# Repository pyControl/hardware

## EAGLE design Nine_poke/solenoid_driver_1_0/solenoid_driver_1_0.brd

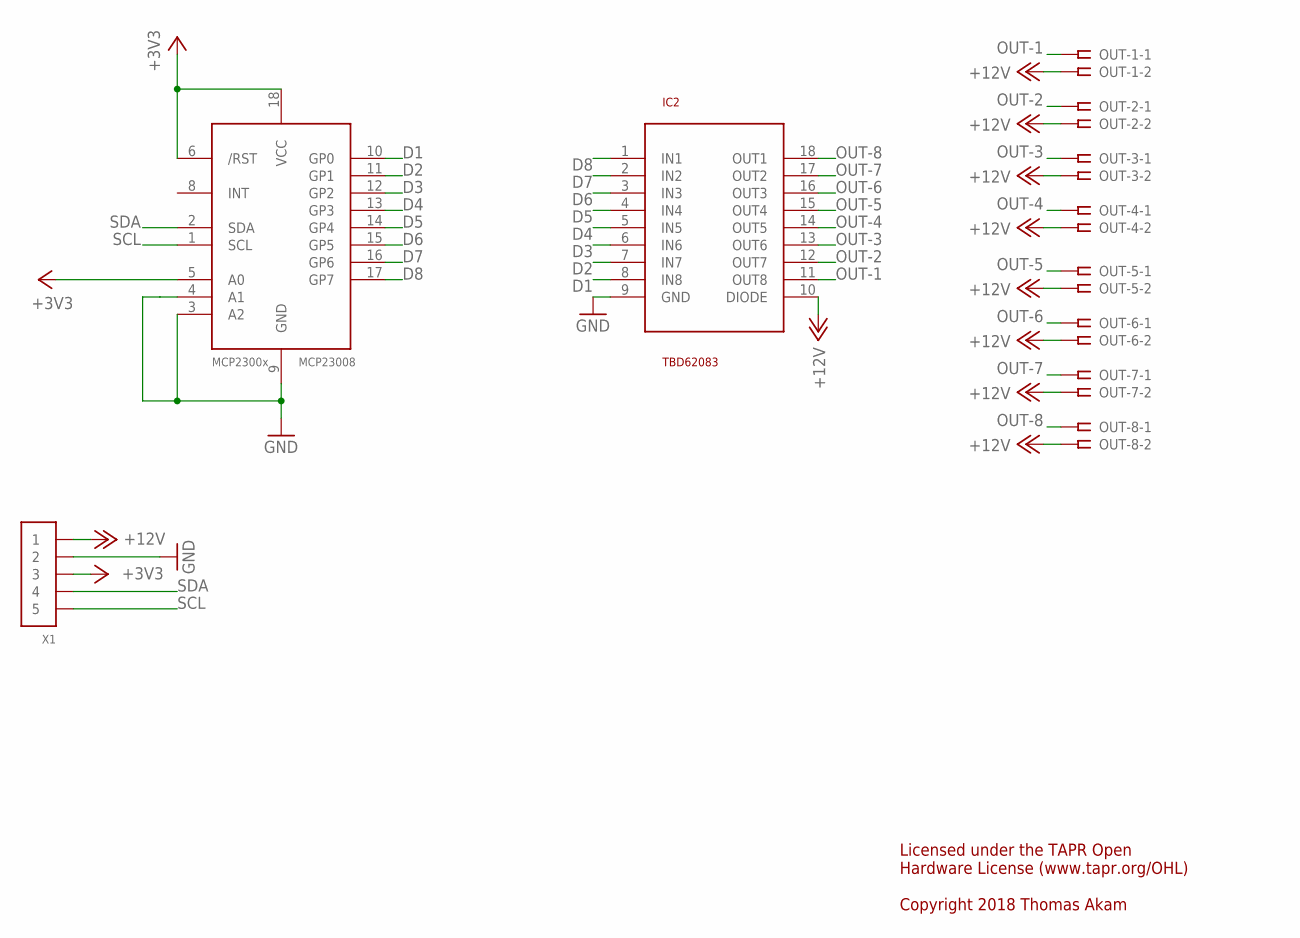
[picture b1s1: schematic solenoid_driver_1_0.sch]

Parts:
IC2: TBD62083; SO18L
MCP23008: MCP2300X/SO; SO18W
OUT-1, OUT-2, OUT-3, OUT-4, OUT-5, OUT-6, OUT-7, OUT-8: SSW-102-02-S-S-RA
X1: CONN_5-1-53261; PB-53261-05

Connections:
+3V3: MCP23008.5 (A0), MCP23008.6 (/RST), MCP23008.18 (VCC), X1.3
+12V: IC2.10 (DIODE), OUT-1.2, OUT-2.2, OUT-3.2, OUT-4.2, OUT-5.2, OUT-6.2, OUT-7.2, OUT-8.2, X1.1
D1: IC2.8 (IN8), MCP23008.10 (GP0)
D2: IC2.7 (IN7), MCP23008.11 (GP1)
D3: IC2.6 (IN6), MCP23008.12 (GP2)
D4: IC2.5 (IN5), MCP23008.13 (GP3)
D5: IC2.4 (IN4), MCP23008.14 (GP4)
D6: IC2.3 (IN3), MCP23008.15 (GP5)
D7: IC2.2 (IN2), MCP23008.16 (GP6)
D8: IC2.1 (IN1), MCP23008.17 (GP7)
GND: IC2.9 (GND), MCP23008.3 (A2), MCP23008.4 (A1), MCP23008.9 (GND), X1.2
OUT-1: IC2.11 (OUT8), OUT-1.1
OUT-2: IC2.12 (OUT7), OUT-2.1
OUT-3: IC2.13 (OUT6), OUT-3.1
OUT-4: IC2.14 (OUT5), OUT-4.1
OUT-5: IC2.15 (OUT4), OUT-5.1
OUT-6: IC2.16 (OUT3), OUT-6.1
OUT-7: IC2.17 (OUT2), OUT-7.1
OUT-8: IC2.18 (OUT1), OUT-8.1
SCL: MCP23008.1 (SCL), X1.5
SDA: MCP23008.2 (SDA), X1.4

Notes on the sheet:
Licensed under the TAPR Open Hardware License (www.tapr.org/OHL) Copyright 2018 Thomas Akam

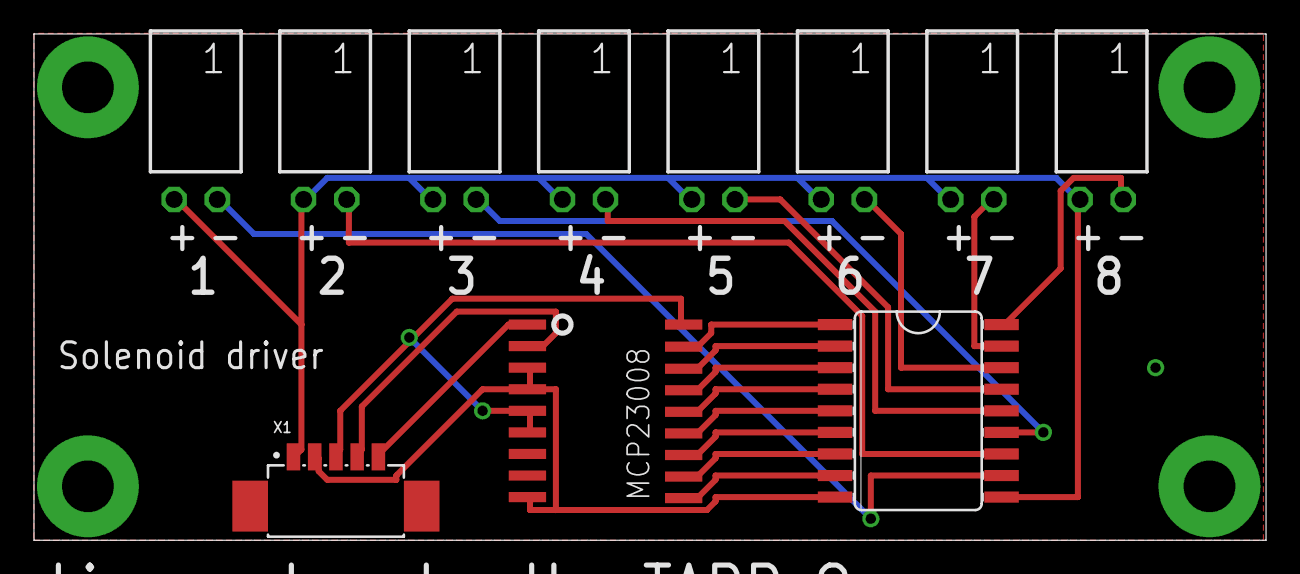
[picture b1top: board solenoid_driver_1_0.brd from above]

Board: 2 copper layers, 72.5 x 29.8 mm, 11 parts (0 on the bottom side), 21 nets.

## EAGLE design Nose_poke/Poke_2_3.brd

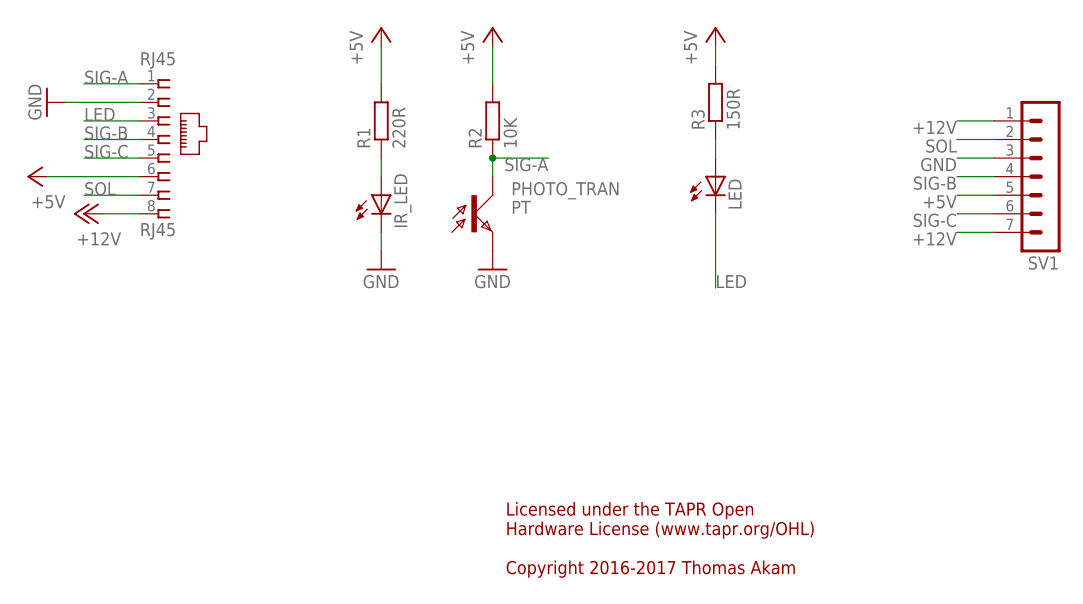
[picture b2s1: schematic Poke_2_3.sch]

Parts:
IR_LED: LEDIRL80A; IRL80A
LED: LEDSML0805; SML0805
PHOTO_TRAN: PT; LPT80A
R1: 220R; R0805
R2: 10K; M0805
R3: 150R; M0805
RJ45: RJ45; RJ45-NO-SHIELD-VERTICAL
SV1: MA07-1

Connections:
+5V: R1.2, R2.2, R3.2, RJ45.6, SV1.5
+12V: RJ45.8, SV1.1, SV1.7
GND: IR_LED.K (C), PHOTO_TRAN.E, RJ45.2, SV1.3
LED: LED.C, RJ45.3
unnamed: IR_LED.A, R1.1
unnamed: LED.A, R3.1
SIG-A: PHOTO_TRAN.C, R2.1, RJ45.1
SIG-B: RJ45.4, SV1.4
SIG-C: RJ45.5, SV1.6
SOL: RJ45.7, SV1.2

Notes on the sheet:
Licensed under the TAPR Open Hardware License (www.tapr.org/OHL) Copyright 2016-2017 Thomas Akam

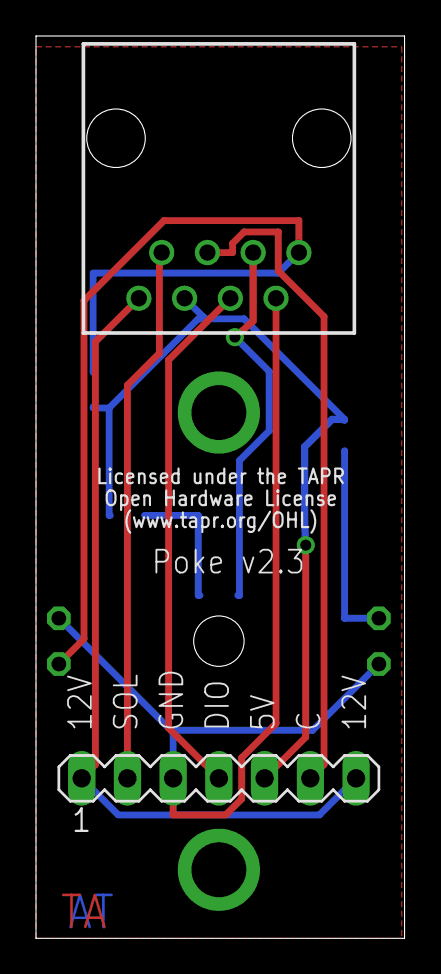
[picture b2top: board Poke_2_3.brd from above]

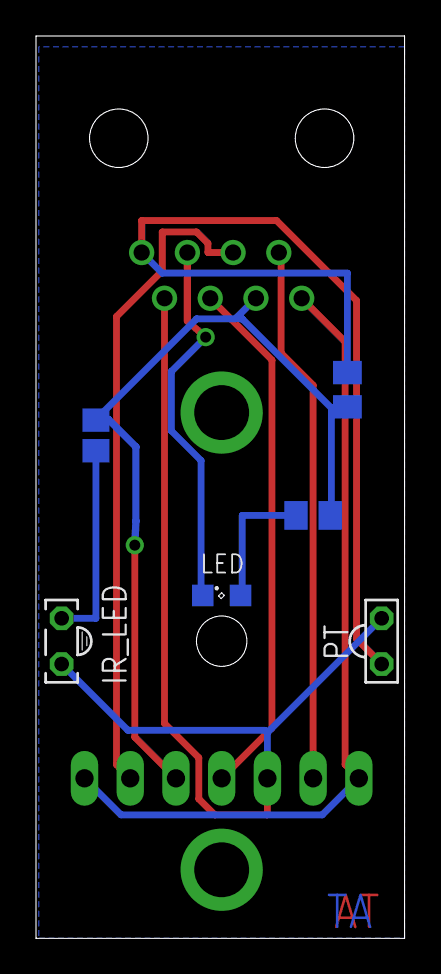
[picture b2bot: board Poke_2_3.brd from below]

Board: 2 copper layers, 20.5 x 50.1 mm, 8 parts (6 on the bottom side), 10 nets.

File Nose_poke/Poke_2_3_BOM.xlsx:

Electronic components
Part | Value | Device | Package | Description | MF | MPN | OC_FARNELL
IR_LED |  | - | - | IR LED side | Sharp | GL480E00000F | 9707794
PHOTO_TRAN |  | - | - | PHOTO TRANSISTOR | OSRAM | SFH3100F-1-Z | 1226443
LED |  | - | 0805 | LED white 0805 | MULTICOMP | OVS-0801 | 1716764
R1 | 220R | - | 0805 | RESISTOR 0805 | MULTICOMP | MC01W08051220R | 9332804
R2 | 10K | - | 0805 | RESISTOR 0805 | MULTICOMP | MC01W0805510K | 9333720
R3 | 150R | - | 0805 | RESISTOR 0805 | MULTICOMP | MC01W08051150R | 9332596
SV1 |  | - | - | Receptacle | AMPHENOL FCI | 76341-307LF | 1098037
RJ45 |  | RJ45VERTICAL | RJ45VERTICAL | RJ45VERTICAL | TE CONNECTIVITY | 5556416-1 | 1773034
Mechanical components
Laser cut plasctic parts as detailed in plastic_parts.pdf
Bolt m3 20mm |  |  |  |  |  |  | 1419947
Bolt m3 20mm |  |  |  |  |  |  | 1419947
Nut m3 |  |  |  |  |  |  | 1420788
Nut m3 |  |  |  |  |  |  | 1420788
Spacer m3, 3mm |  |  |  |  |  |  | 359154
Spacer m3, 3mm |  |  |  |  |  |  | 359154
Licensed under the TAPR Open Hardware License (www.tapr.org/OHL)
Copyright 2016-2017 Thomas Akam

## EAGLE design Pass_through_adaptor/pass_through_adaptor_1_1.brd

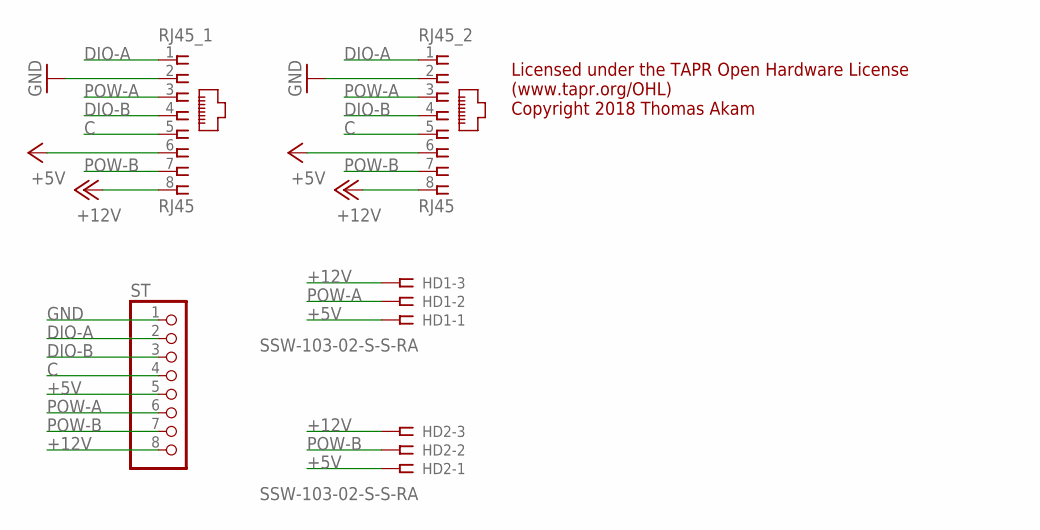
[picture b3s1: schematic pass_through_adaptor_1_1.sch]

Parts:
HD1, HD2: SSW-103-02-S-S-RA
RJ45_1, RJ45_2: RJ45; RJ45-NO-SHIELD-VERTICAL
ST: PINHD-1X8; 1X08

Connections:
+5V: HD1.1, HD2.1, RJ45_1.6, RJ45_2.6, ST.5
+12V: HD1.3, HD2.3, RJ45_1.8, RJ45_2.8, ST.8
C: RJ45_1.5, RJ45_2.5, ST.4
DIO-A: RJ45_1.1, RJ45_2.1, ST.2
DIO-B: RJ45_1.4, RJ45_2.4, ST.3
GND: RJ45_1.2, RJ45_2.2, ST.1
POW-A: HD1.2, RJ45_1.3, RJ45_2.3, ST.6
POW-B: HD2.2, RJ45_1.7, RJ45_2.7, ST.7

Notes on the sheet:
Licensed under the TAPR Open Hardware License (www.tapr.org/OHL) Copyright 2018 Thomas Akam

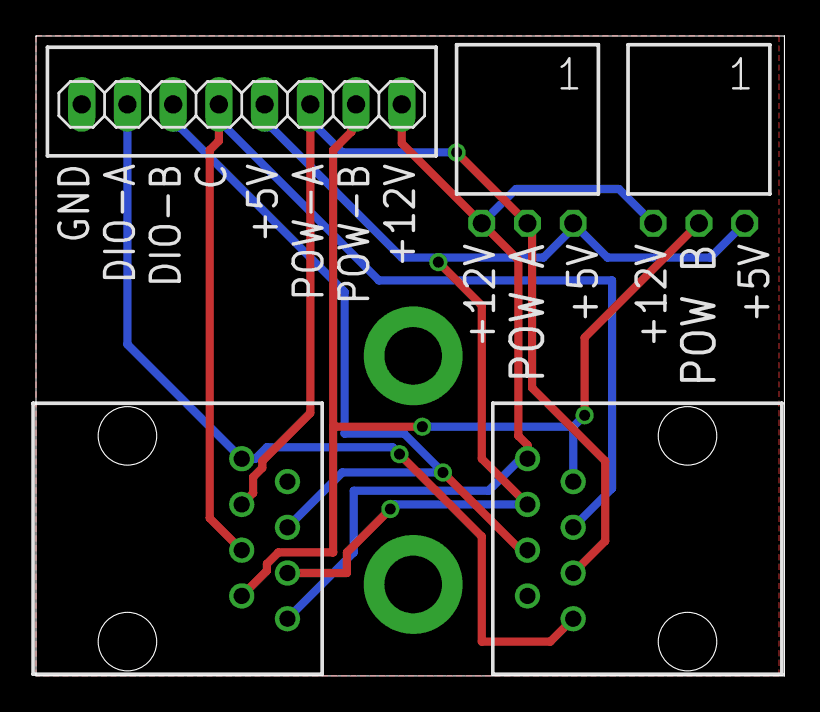
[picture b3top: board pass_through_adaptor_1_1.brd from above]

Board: 2 copper layers, 41.6 x 35.5 mm, 5 parts (0 on the bottom side), 8 nets.

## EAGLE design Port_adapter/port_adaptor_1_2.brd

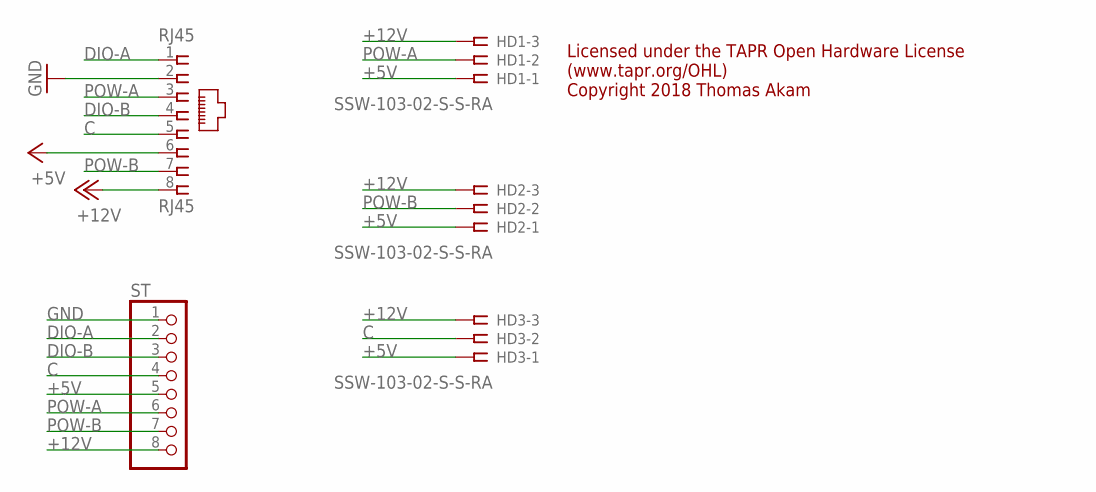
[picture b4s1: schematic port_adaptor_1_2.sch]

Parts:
HD1, HD2, HD3: SSW-103-02-S-S-RA
RJ45: RJ45; RJ45-NO-SHIELD-VERTICAL
ST: PINHD-1X8; 1X08

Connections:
+5V: HD1.1, HD2.1, HD3.1, RJ45.6, ST.5
+12V: HD1.3, HD2.3, HD3.3, RJ45.8, ST.8
C: HD3.2, RJ45.5, ST.4
DIO-A: RJ45.1, ST.2
DIO-B: RJ45.4, ST.3
GND: RJ45.2, ST.1
POW-A: HD1.2, RJ45.3, ST.6
POW-B: HD2.2, RJ45.7, ST.7

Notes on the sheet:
Licensed under the TAPR Open Hardware License (www.tapr.org/OHL) Copyright 2018 Thomas Akam

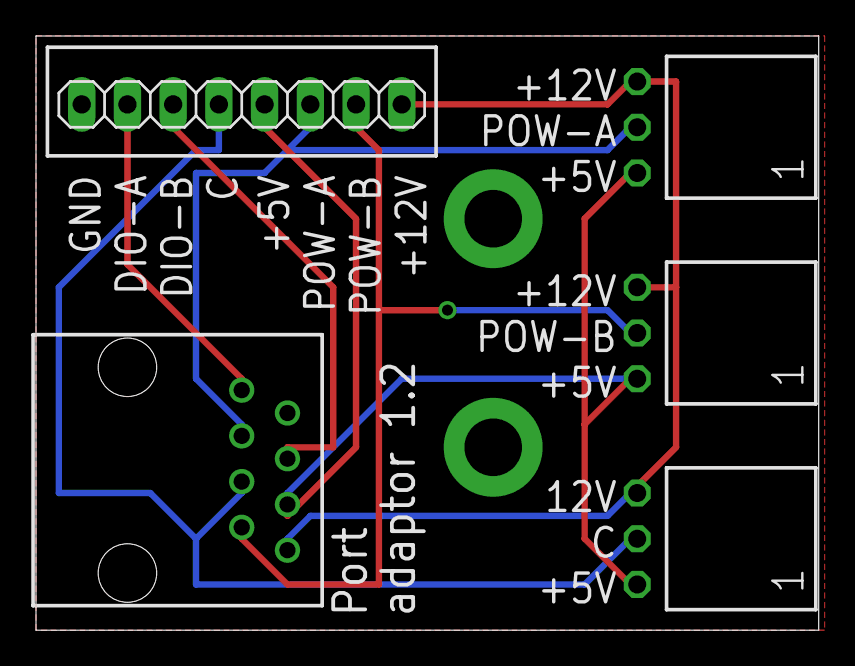
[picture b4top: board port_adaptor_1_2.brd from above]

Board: 2 copper layers, 43.5 x 33.0 mm, 5 parts (0 on the bottom side), 8 nets.

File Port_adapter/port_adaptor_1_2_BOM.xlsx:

Part | Value | Device | Package | Description | MF | MPN | OC_FARNELL
HD1 | - | - | - | 3 way female header RA | SAMTEC | SSW-103-02-T-S-RA | 1803357
HD2 | - | - | - | 3 way female header RA | SAMTEC | SSW-103-02-T-S-RA | 1803357
HD3 | - | - | - | 3 way female header RA | SAMTEC | SSW-103-02-T-S-RA | 1803357
RJ45 | - | - | - | RJ45Horisontal | TE CONNECTIVITY | 215877-1 | 3363144
ST | - | - | - | Screw terminal | PHOENIX CONTACT | 1725711 | 3041438
Licensed under the TAPR Open Hardware License
(www.tapr.org/OHL)
Copyright 2018 Thomas Akam

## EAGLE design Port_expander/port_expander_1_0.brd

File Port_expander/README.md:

# Port Expander

The port expander board uses i2c serial to parallel IO expander ICs to run 8 behaviour ports from a single behaviour port on the breakout board.  

[Documentation](https://pycontrol.readthedocs.io/en/latest/user-guide/hardware/#port-expander)

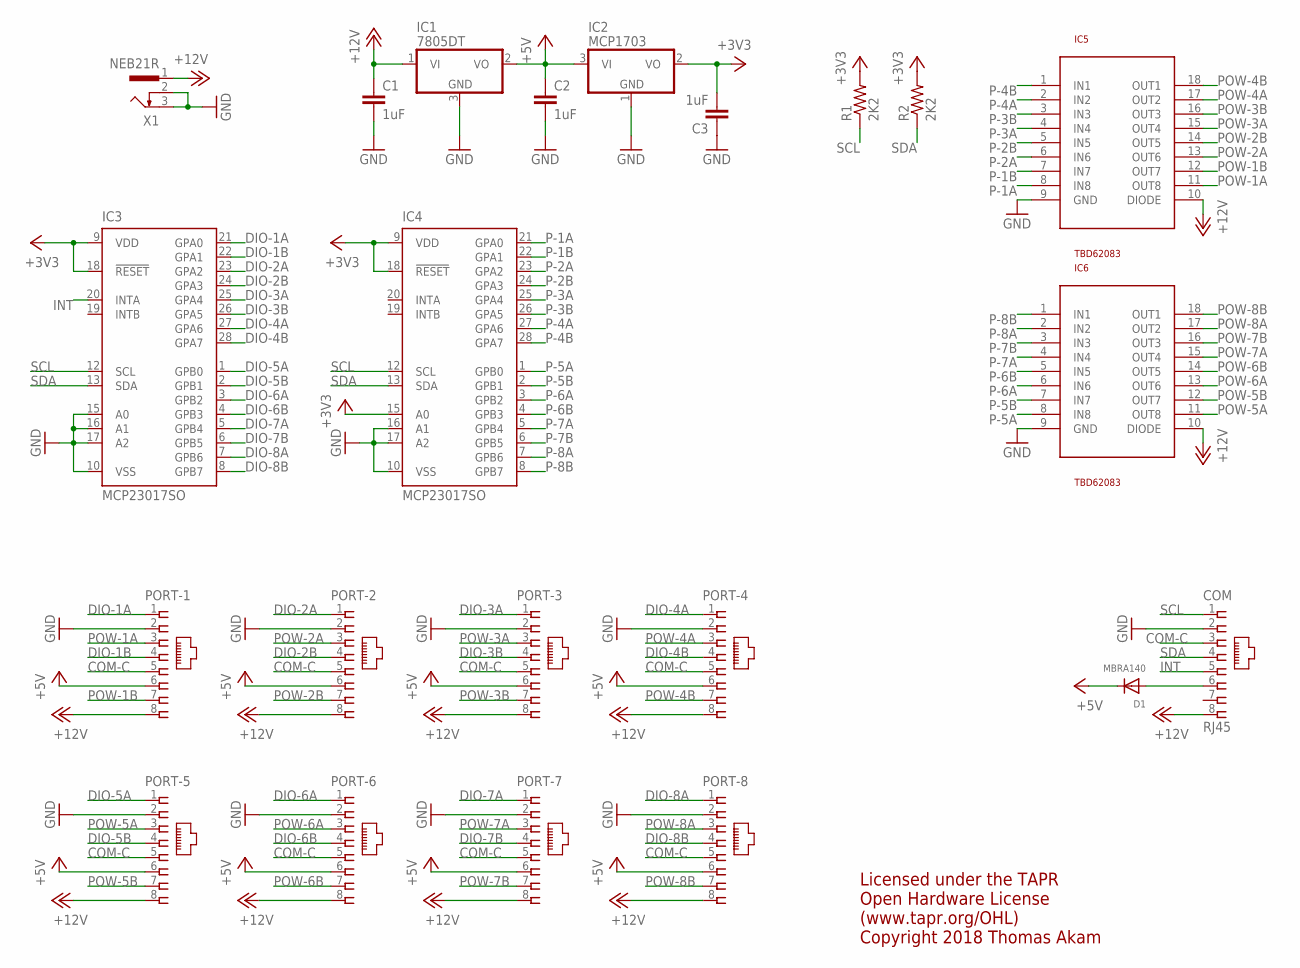
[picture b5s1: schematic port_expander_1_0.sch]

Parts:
C1, C2, C3: 1uF; C0805
COM: RJ45; RJ45-NO-SHIELD-VERTICAL
D1: MBRA140; SOD-123
IC1: 7805DT; TO252
IC2: MCP1703; SOT23
IC3, IC4: MCP23017SO; SO28W
IC5, IC6: TBD62083; SO18L
PORT-1, PORT-2, PORT-3, PORT-4, PORT-5, PORT-6, PORT-7, PORT-8: RJ45VERTICAL; RJ45-NO-SHIELD-VERTICAL
R1, R2: 2K2; 0805
X1: NEB21R

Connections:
+3V3: C3.2, IC2.2 (VO), IC3.9 (VDD), IC3.18 (!RESET), IC4.9 (VDD), IC4.15 (A0), IC4.18 (!RESET), R1.2, R2.2
+5V: C2.1, D1.C, IC1.2 (VO), IC2.3 (VI), PORT-1.6, PORT-2.6, PORT-3.6, PORT-4.6, PORT-5.6, PORT-6.6, PORT-7.6, PORT-8.6
+12V: C1.1, COM.8, IC1.1 (VI), IC5.10 (DIODE), IC6.10 (DIODE), PORT-1.8, PORT-2.8, PORT-3.8, PORT-4.8, PORT-5.8, PORT-6.8, PORT-7.8, PORT-8.8, X1.1
COM-C: COM.3, PORT-1.5, PORT-2.5, PORT-3.5, PORT-4.5, PORT-5.5, PORT-6.5, PORT-7.5, PORT-8.5
DIO-1A: IC3.21 (GPA0), PORT-1.1
DIO-1B: IC3.22 (GPA1), PORT-1.4
DIO-2A: IC3.23 (GPA2), PORT-2.1
DIO-2B: IC3.24 (GPA3), PORT-2.4
DIO-3A: IC3.25 (GPA4), PORT-3.1
DIO-3B: IC3.26 (GPA5), PORT-3.4
DIO-4A: IC3.27 (GPA6), PORT-4.1
DIO-4B: IC3.28 (GPA7), PORT-4.4
DIO-5A: IC3.1 (GPB0), PORT-5.1
DIO-5B: IC3.2 (GPB1), PORT-5.4
DIO-6A: IC3.3 (GPB2), PORT-6.1
DIO-6B: IC3.4 (GPB3), PORT-6.4
DIO-7A: IC3.5 (GPB4), PORT-7.1
DIO-7B: IC3.6 (GPB5), PORT-7.4
DIO-8A: IC3.7 (GPB6), PORT-8.1
DIO-8B: IC3.8 (GPB7), PORT-8.4
GND: C1.2, C2.2, C3.1, COM.2, IC1.3 (GND), IC2.1 (GND), IC3.10 (VSS), IC3.15 (A0), IC3.16 (A1), IC3.17 (A2), IC4.10 (VSS), IC4.16 (A1), IC4.17 (A2), IC5.9 (GND), IC6.9 (GND), PORT-1.2, PORT-2.2, PORT-3.2, PORT-4.2, PORT-5.2, PORT-6.2, PORT-7.2, PORT-8.2, X1.2, X1.3
INT: COM.5, IC3.20 (INTA)
unnamed: COM.6, D1.A
P-1A: IC4.21 (GPA0), IC5.8 (IN8)
P-1B: IC4.22 (GPA1), IC5.7 (IN7)
P-2A: IC4.23 (GPA2), IC5.6 (IN6)
P-2B: IC4.24 (GPA3), IC5.5 (IN5)
P-3A: IC4.25 (GPA4), IC5.4 (IN4)
P-3B: IC4.26 (GPA5), IC5.3 (IN3)
P-4A: IC4.27 (GPA6), IC5.2 (IN2)
P-4B: IC4.28 (GPA7), IC5.1 (IN1)
P-5A: IC4.1 (GPB0), IC6.8 (IN8)
P-5B: IC4.2 (GPB1), IC6.7 (IN7)
P-6A: IC4.3 (GPB2), IC6.6 (IN6)
P-6B: IC4.4 (GPB3), IC6.5 (IN5)
P-7A: IC4.5 (GPB4), IC6.4 (IN4)
P-7B: IC4.6 (GPB5), IC6.3 (IN3)
P-8A: IC4.7 (GPB6), IC6.2 (IN2)
P-8B: IC4.8 (GPB7), IC6.1 (IN1)
POW-1A: IC5.11 (OUT8), PORT-1.3
POW-1B: IC5.12 (OUT7), PORT-1.7
POW-2A: IC5.13 (OUT6), PORT-2.3
POW-2B: IC5.14 (OUT5), PORT-2.7
POW-3A: IC5.15 (OUT4), PORT-3.3
POW-3B: IC5.16 (OUT3), PORT-3.7
POW-4A: IC5.17 (OUT2), PORT-4.3
POW-4B: IC5.18 (OUT1), PORT-4.7
POW-5A: IC6.11 (OUT8), PORT-5.3
POW-5B: IC6.12 (OUT7), PORT-5.7
POW-6A: IC6.13 (OUT6), PORT-6.3
POW-6B: IC6.14 (OUT5), PORT-6.7
POW-7A: IC6.15 (OUT4), PORT-7.3
POW-7B: IC6.16 (OUT3), PORT-7.7
POW-8A: IC6.17 (OUT2), PORT-8.3
POW-8B: IC6.18 (OUT1), PORT-8.7
SCL: COM.1, IC3.12 (SCL), IC4.12 (SCL), R1.1
SDA: COM.4, IC3.13 (SDA), IC4.13 (SDA), R2.1

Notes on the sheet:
Licensed under the TAPR Open Hardware License (www.tapr.org/OHL) Copyright 2018 Thomas Akam

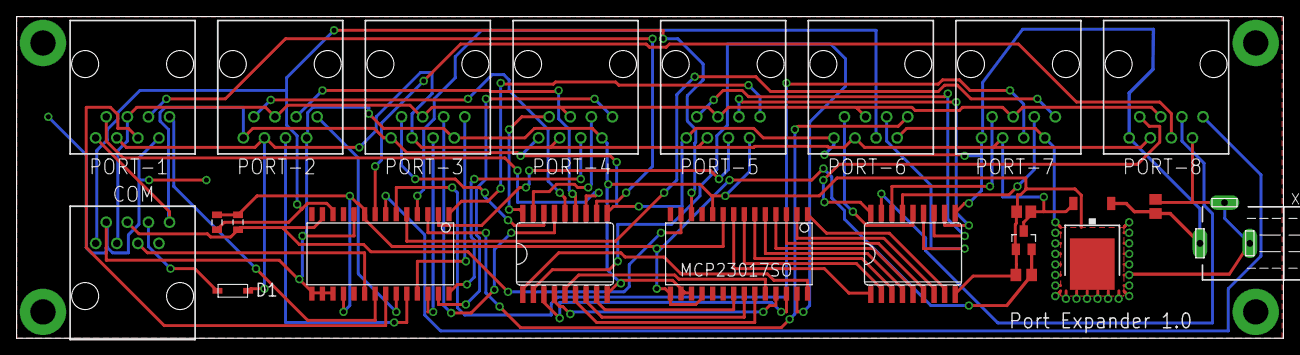
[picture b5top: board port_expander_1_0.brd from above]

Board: 2 copper layers, 152.6 x 38.7 mm, 22 parts (0 on the bottom side), 57 nets.

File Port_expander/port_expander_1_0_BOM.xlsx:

Part | Value | Device | Package | Description | MF | MPN | OC_FARNELL
R1 | 2K2 | - | 0805 | Resistor 0805 | Multicomp | MCWR08X2201FTL | 2447623
R2 | 2K2 | - | 0805 | Resistor 0805 | Multicomp | MCWR08X2201FTL | 2447623
C1 | 1uF | - | 0805 | capacitor 0805 | Multicomp | MC0805B105K250CT | 2320827
C2 | 1uF | - | 0805 | capacitor 0805 | Multicomp | MC0805B105K250CT | 2320827
C3 | 1uF | - | 0805 | capacitor 0805 | Multicomp | MC0805B105K250CT | 2320827
D1 | - | - | SOD-123FL | DIODE | ON SEMICONDUCTOR | MBR120VLSFT3G | 2533227
IC1 | - | 7805 | TO-252-3 | VOLTAGE REGULATOR | ON SEMICONDUCTOR | MC7805BDTRKG | 1652297
IC2 | - | MCP1703T | SOT-23 | Voltage regulator 3v3 | MICROCHIP | MCP1703T-3302E/CB | 1439518
IC3 | - | MCP23017 | SO28 | i2c port expander | MICROCHIP | MCP23017-E/SO | 1332087
IC4 | - | MCP23017 | SO28 | i2c port expander | MICROCHIP | MCP23017-E/SO | 1332087
IC5 |  | TBD62083 | SO18 | Low side driver | Toshiba | TBD62083AFG | -
IC6 |  | TBD62083 | SO18 | Low side driver | Toshiba | TBD62083AFG | -
PORT1 |  | - | - | RJ45Horisontal | TE CONNECTIVITY | 215877-1 | 3363144
PORT2 |  | - | - | RJ45Horisontal | TE CONNECTIVITY | 215877-1 | 3363144
PORT3 |  | - | - | RJ45Horisontal | TE CONNECTIVITY | 215877-1 | 3363144
PORT4 |  | - | - | RJ45Horisontal | TE CONNECTIVITY | 215877-1 | 3363144
PORT5 |  | - | - | RJ45Horisontal | TE CONNECTIVITY | 215877-1 | 3363144
PORT6 |  | - | - | RJ45Horisontal | TE CONNECTIVITY | 215877-1 | 3363144
PORT7 |  | - | - | RJ45Horisontal | TE CONNECTIVITY | 215877-1 | 3363144
PORT8 |  | - | - | RJ45Horisontal | TE CONNECTIVITY | 215877-1 | 3363144
COM |  | - | - | RJ45Horisontal | TE CONNECTIVITY | 215877-1 | 3363144
POW_CON |  | NEB21R | NEB21R | 2.1mm socket | Lumberg | NEB 21 R | 1217037
Licensed under the TAPR Open Hardware License (www.tapr.org/OHL)
Copyright 2018 Thomas Akam

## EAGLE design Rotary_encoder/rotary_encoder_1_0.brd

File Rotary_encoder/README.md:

# Rotary encoder

Board for connecting an Avago HEDM or HEDS series rotary encoder to a pyControl behaviour port.

[Documentation](https://pycontrol.readthedocs.io/en/latest/user-guide/hardware/#rotary-encoder)

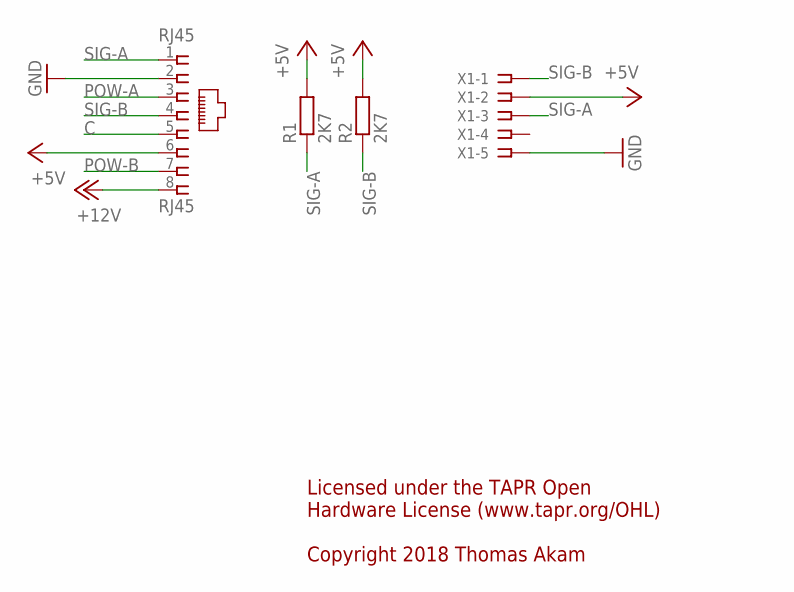
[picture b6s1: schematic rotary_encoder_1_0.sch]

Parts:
R1, R2: 2K7; M0805
RJ45: RJ45; RJ45-NO-SHIELD-VERTICAL
X1: SSW-105-02-S-S-RA

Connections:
+5V: R1.2, R2.2, RJ45.6, X1.2
+12V: RJ45.8
C: RJ45.5
GND: RJ45.2, X1.5
POW-A: RJ45.3
POW-B: RJ45.7
SIG-A: R1.1, RJ45.1, X1.3
SIG-B: R2.1, RJ45.4, X1.1

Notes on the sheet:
Licensed under the TAPR Open Hardware License (www.tapr.org/OHL) Copyright 2018 Thomas Akam

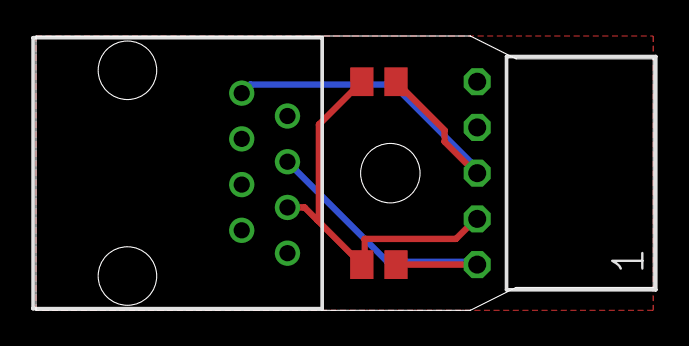
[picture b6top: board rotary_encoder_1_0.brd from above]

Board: 2 copper layers, 34.3 x 15.2 mm, 4 parts (0 on the bottom side), 4 nets.

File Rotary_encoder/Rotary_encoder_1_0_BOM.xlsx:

Part | Value | Device | Package | Description | MF | MPN | OC_FARNELL
X1 | - | - | - | 5 way RA receptacle | Samtec | SSW-105-02-G-S-RA | 1668350
RJ45 | - | - | - | RJ45 Horisontal | TE CONNECTIVITY | 215877-1 | 3363144
R1 | 2K7 | - | 0805 | Resistor 0805 | Multicomp | MCWR08X2701FTL | 2447627
R2 | 2K7 | - | 0805 | Resistor 0805 | Multicomp | MCWR08X2701FTL | 2447627
Licensed under the TAPR Open Hardware License (www.tapr.org/OHL)
Copyright 2018 Thomas Akam
Licensed under the TAPR Open Hardware License (www.tapr.org/OHL)
Copyright 2016-2017 Thomas Akam

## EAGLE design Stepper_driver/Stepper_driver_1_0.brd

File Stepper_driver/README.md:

# Stepper motor driver

Board for connecting an [EasyDriver](http://www.schmalzhaus.com/EasyDriver/) stepper motor driver to a pyControl behaviour port.

[Documentation](https://pycontrol.readthedocs.io/en/latest/user-guide/hardware/#stepper-motor)

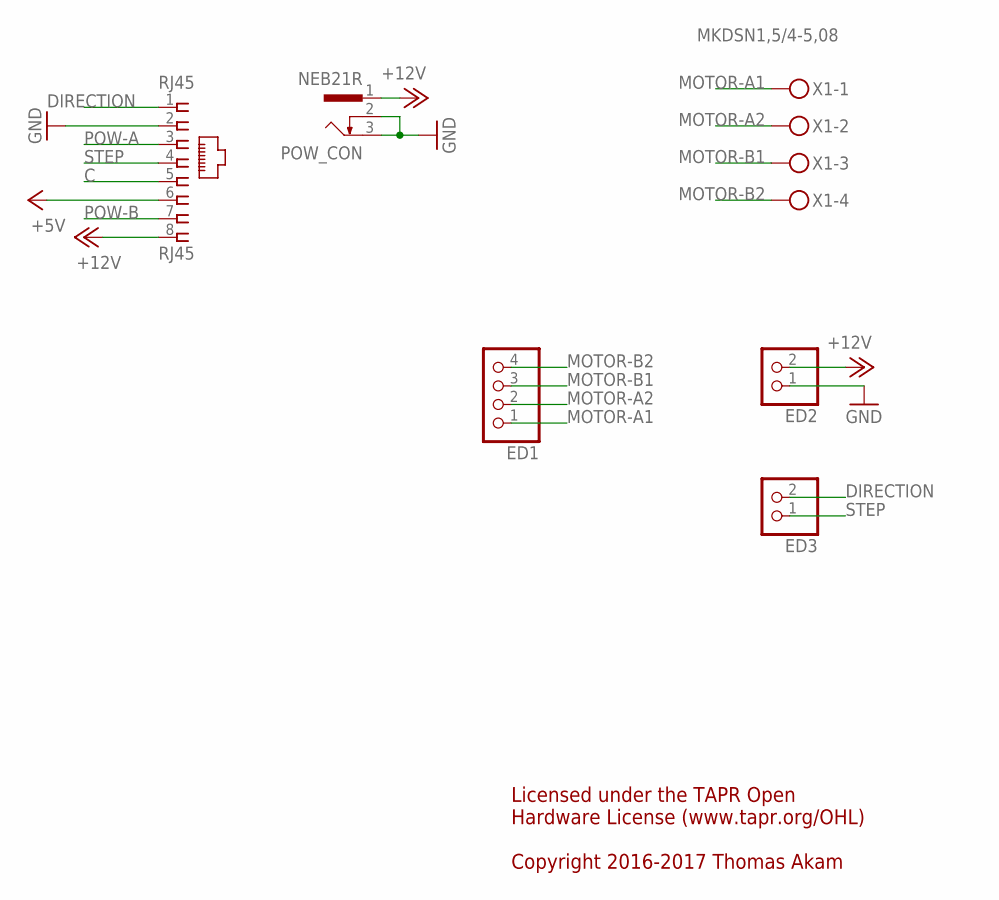
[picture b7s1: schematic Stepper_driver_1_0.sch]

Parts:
ED1: PINHD-1X4; 1X04
ED2, ED3: PINHD-1X2; 1X02
POW_CON: NEB21R
RJ45: RJ45; RJ45-NO-SHIELD-VERTICAL
X1: MKDSN1,5/4-5,08

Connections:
+5V: RJ45.6
+12V: ED2.2, POW_CON.1, RJ45.8
C: RJ45.5
DIRECTION: ED3.2, RJ45.1
GND: ED2.1, POW_CON.2, POW_CON.3, RJ45.2
MOTOR-A1: ED1.1, X1.1
MOTOR-A2: ED1.2, X1.2
MOTOR-B1: ED1.3, X1.3
MOTOR-B2: ED1.4, X1.4
POW-A: RJ45.3
POW-B: RJ45.7
STEP: ED3.1, RJ45.4

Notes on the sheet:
Licensed under the TAPR Open Hardware License (www.tapr.org/OHL) Copyright 2016-2017 Thomas Akam

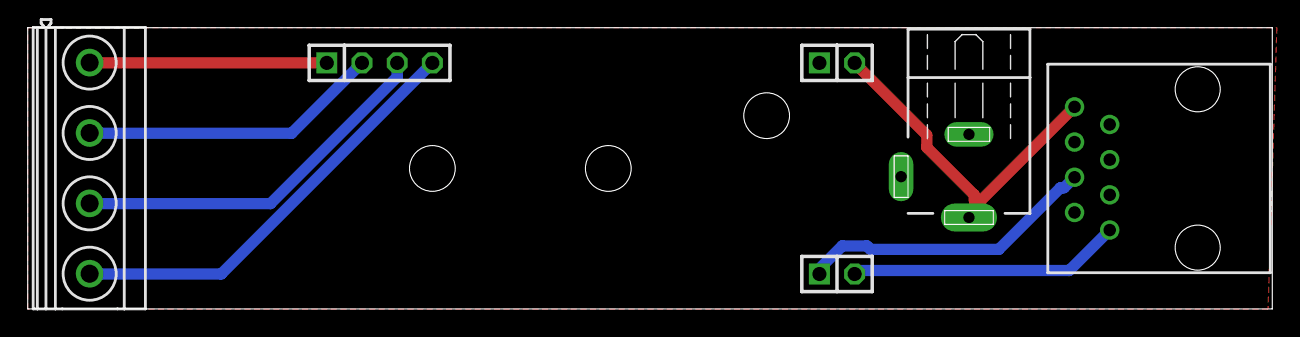
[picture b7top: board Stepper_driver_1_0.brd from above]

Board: 2 copper layers, 89.8 x 20.3 mm, 6 parts (0 on the bottom side), 8 nets.

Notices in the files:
parts and their libraries:
SparkFun-Resistors: Licensing: CC v3.0 Share-Alike You are welcome to use this library for commercial purposes.
